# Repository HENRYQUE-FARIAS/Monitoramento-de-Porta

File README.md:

# Monitoramento-de-Porta
V1.0
versão 1.0 sitema monitora o status de sensores de porta, placa de desenvolvimento wt32-eth01 conta com microcontrolador ESP32 essa placa possui entrada ETH para conexão de rede, wifi e bluetooth. o firmware conta com uma página web individual e um sistema que permite agrupar cada dispositivo em uma tela única através do direcionamento IP.

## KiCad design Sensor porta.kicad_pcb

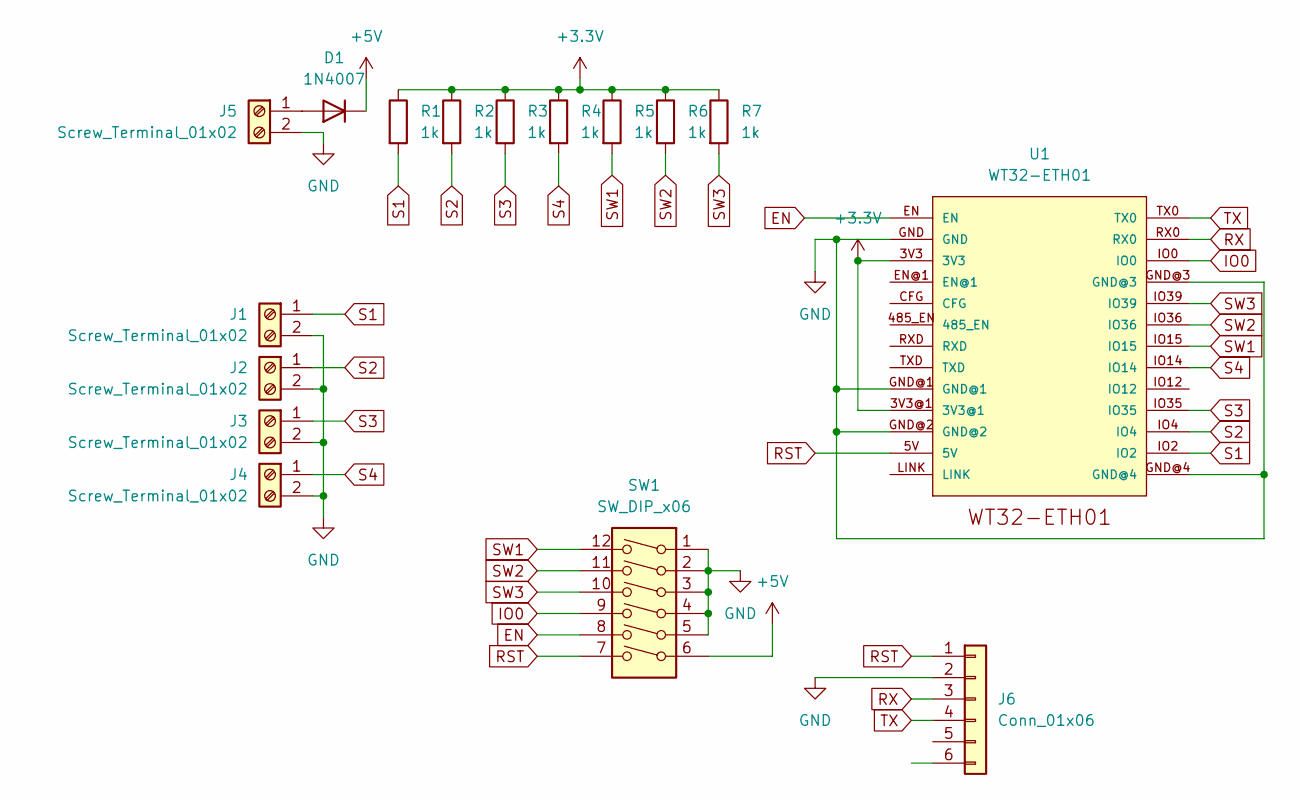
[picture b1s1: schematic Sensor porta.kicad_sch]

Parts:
D1: 1N4007; D_DO-41_SOD81_P10.16mm_Horizontal
J1, J2, J3, J4, J5: Screw_Terminal_01x02; TerminalBlock_Phoenix_MKDS-1,5-2_1x02_P5.00mm_Horizontal
J6: Conn_01x06; PinSocket_1x06_P2.54mm_Vertical
R1, R2, R3, R4, R5, R6, R7: 1k; R_Axial_DIN0207_L6.3mm_D2.5mm_P10.16mm_Horizontal
SW1: SW_DIP_x06; SW_DIP_SPSTx06_Slide_9.78x17.42mm_W7.62mm_P2.54mm
U1: WT32-ETH01

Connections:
+3.3V: R1.1, R2.1, R3.1, R4.1, R5.1, R6.1, R7.1, U1.3V3, U1.3V3@1
+5V: D1.1 (K), SW1.6
EN: SW1.8, U1.EN
GND: J1.2, J2.2, J3.2, J4.2, J5.2, J6.2, SW1.1, SW1.2, SW1.3, SW1.4, SW1.5, U1.GND, U1.GND@1, U1.GND@2, U1.GND@3, U1.GND@4
IO0: SW1.9, U1.IO0
unnamed: D1.2 (A), J5.1
RST: J6.1, SW1.7, U1.5V
RX: J6.3, U1.RX0
S1: J1.1, R1.2, U1.IO2
S2: J2.1, R2.2, U1.IO4
S3: J3.1, R3.2, U1.IO35
S4: J4.1, R4.2, U1.IO14
SW1: R5.2, SW1.12, U1.IO15
SW2: R6.2, SW1.11, U1.IO36
SW3: R7.2, SW1.10, U1.IO39
TX: J6.4, U1.TX0

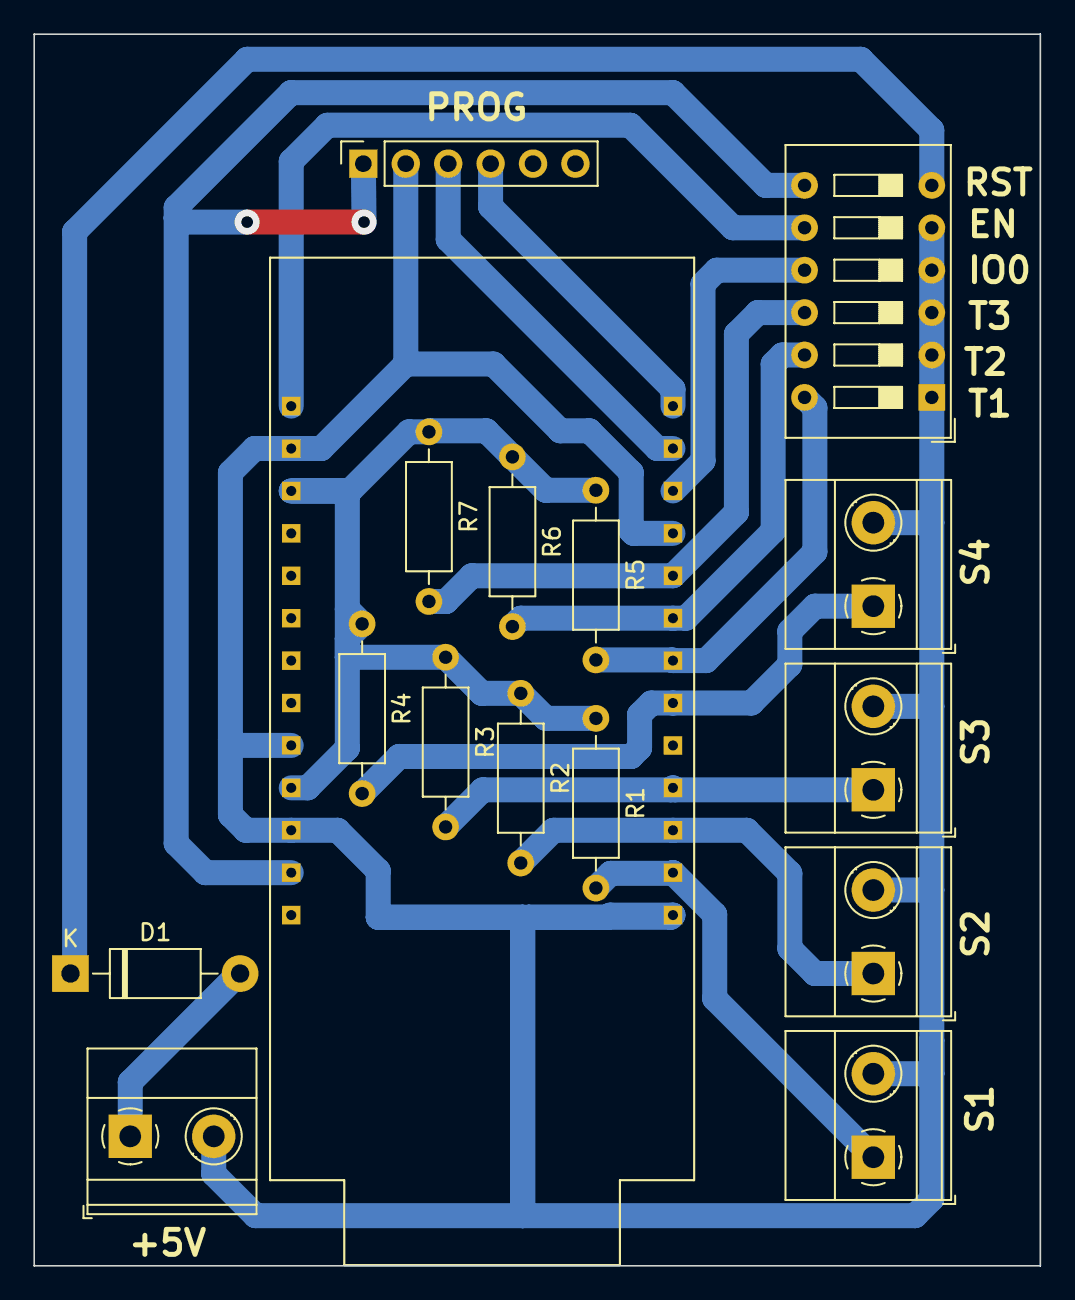
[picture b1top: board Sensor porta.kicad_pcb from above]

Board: 2 copper layers, 60.3 x 73.8 mm, 16 parts (0 on the bottom side), 16 nets.
